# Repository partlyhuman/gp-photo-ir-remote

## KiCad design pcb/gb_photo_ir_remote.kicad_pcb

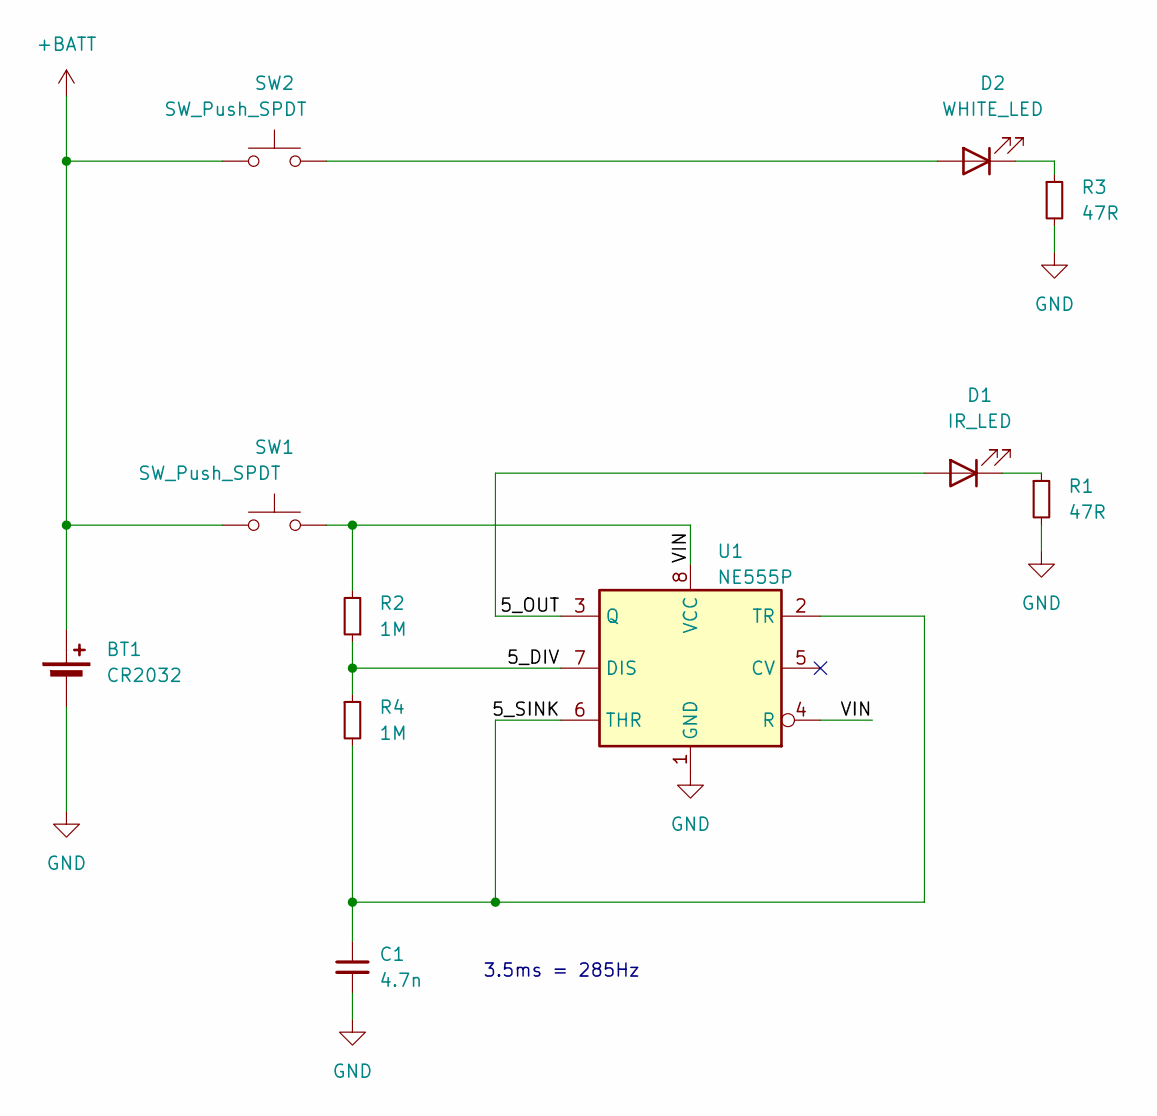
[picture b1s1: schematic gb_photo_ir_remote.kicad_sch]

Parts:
BT1: CR2032; REB_BatteryHolder_2032
C1: 4.7n; C_Disc_D5.0mm_W2.5mm_P5.00mm
D1: IR_LED; LED_D5.0mm_Horizontal_O1.27mm_Z3.0mm
D2: WHITE_LED; LED_D5.0mm_Horizontal_O1.27mm_Z3.0mm
R1, R3: 47R; R_Axial_DIN0207_L6.3mm_D2.5mm_P10.16mm_Horizontal
R2, R4: 1M; R_Axial_DIN0207_L6.3mm_D2.5mm_P10.16mm_Horizontal
SW1, SW2: SW_Push_SPDT; SW_PUSH_6mm
U1: NE555P; DIP-8_W7.62mm

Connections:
+BATT: BT1.1 (+), SW1.1, SW2.1
/5_DIV: R2.1, R4.1, U1.7 (DIS)
/5_OUT: D1.2 (A), U1.3 (Q)
/5_SINK: C1.1, R4.2, U1.2 (TR), U1.6 (THR)
/VIN: R2.2, SW1.2, U1.4 (R), U1.8 (VCC)
GND: BT1.2 (-), C1.2, R1.2, R3.2, U1.1 (GND)
unnamed: D1.1 (K), R1.1
unnamed: D2.2 (A), SW2.2
unnamed: D2.1 (K), R3.1

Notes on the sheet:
3.5ms = 285Hz

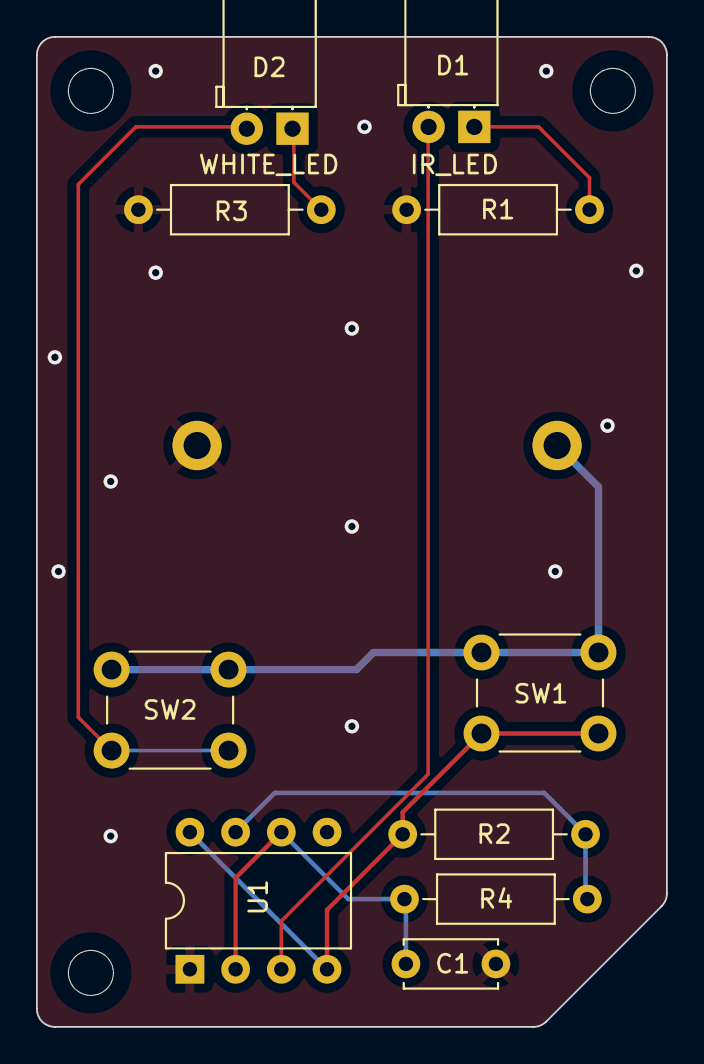
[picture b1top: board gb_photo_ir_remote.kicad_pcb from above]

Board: 2 copper layers, 35.0 x 55.0 mm, 14 parts (1 on the bottom side), 9 nets.

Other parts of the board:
M1, M2, M3: MountingHole_2.5mm

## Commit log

2023-12-14 tiny CR2032 IR flasher
2023-12-14 init
2023-12-15 build
2024-01-03 Timer didn't use an actual divider?
